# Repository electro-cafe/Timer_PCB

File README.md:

# Timer_PCB
This repository contain all file relative to the PCB of the timer project.

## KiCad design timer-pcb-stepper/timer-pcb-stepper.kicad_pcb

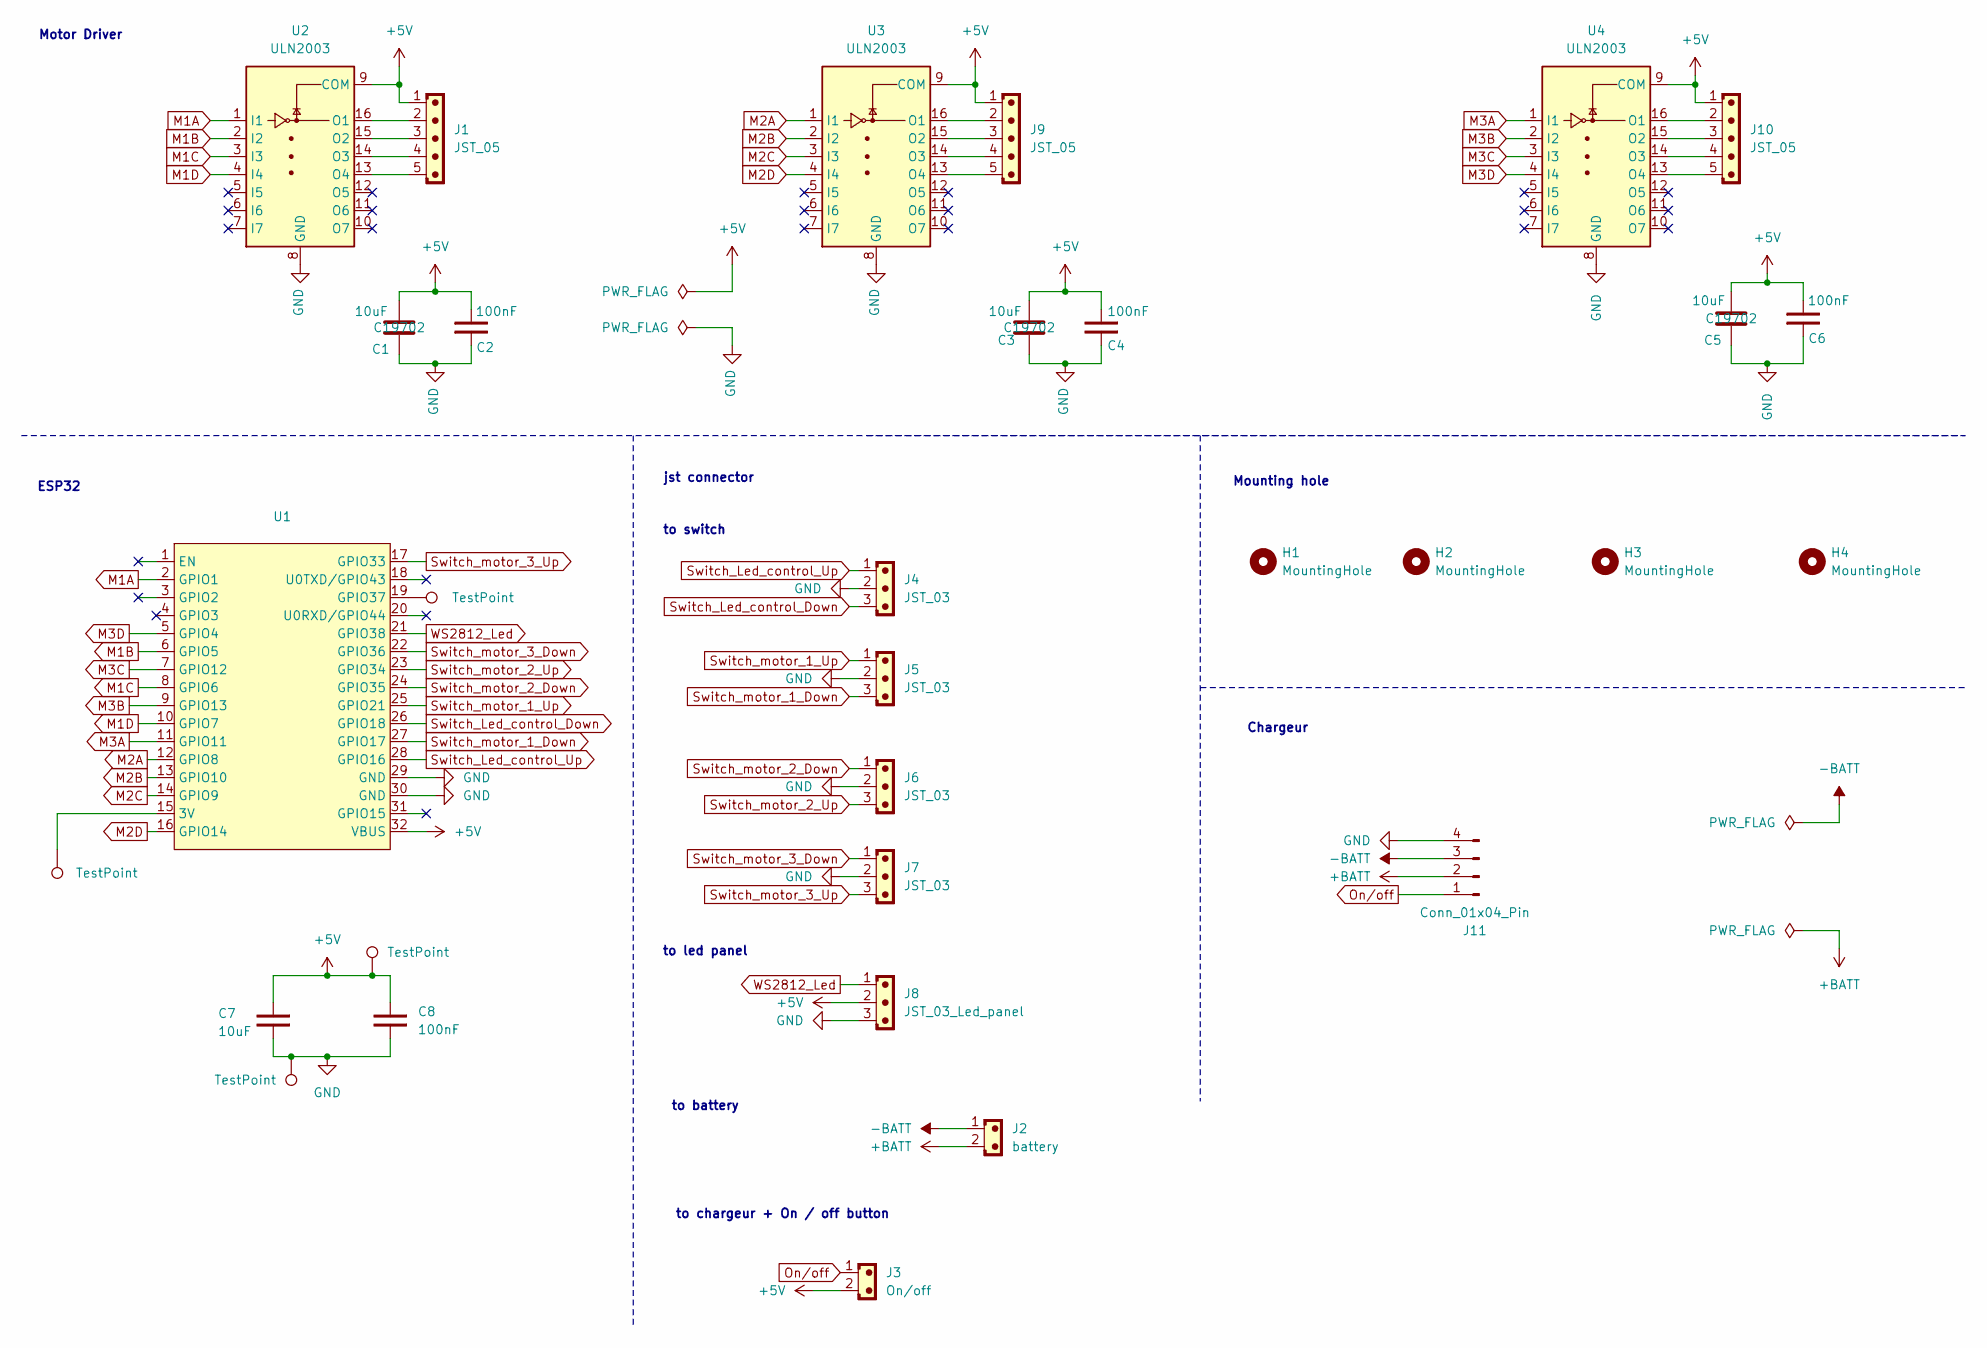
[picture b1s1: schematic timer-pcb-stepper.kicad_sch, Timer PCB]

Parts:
C1, C3, C5, C7: 10uF; C_0805_2012Metric; JLCPCB Part # C19702
C2, C4, C6, C8: 100nF; C_0603_1608Metric; JLCPCB Part # C1525
H1, H2, H3, H4: MountingHole; MountingHole_3.2mm_M3_DIN965_Pad_TopOnly
J1, J9, J10: JST_05; JST_EH_B5B-EH-A_1x05_P2.50mm_Vertical; JLCPCB Part # C157991
J2: battery; JST_XH_B2B-XH-AM_1x02_P2.50mm_Vertical
J3: On/off; JST_XH_B2B-XH-AM_1x02_P2.50mm_Vertical
J4, J5, J6, J7: JST_03; JST_XH_S3B-XH-A-1_1x03_P2.50mm_Horizontal
J8: JST_03_Led_panel; JST_XH_S3B-XH-A-1_1x03_P2.50mm_Horizontal
J11: Conn_01x04_Pin; JST_XA_B04B-XASK-1-A_1x04_P2.50mm_Vertical
TP1, TP2, TP3, TP4: TestPoint; TestPoint_Loop_D2.54mm_Drill1.5mm_Beaded
U1: S3 Mini
U2, U3, U4: ULN2003; SOIC-16_4.55x10.3mm_P1.27mm; LCSC C7512

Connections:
+5V: C1.2, C2.2, C3.2, C4.1, C5.2, C6.2, C7.1, C8.1, J1.1, J3.2, J8.2, J9.1, J10.1, TP2.1, U1.32 (VBUS), U2.9 (COM), U3.9 (COM), U4.9 (COM)
+BATT: J2.2, J11.2
-BATT: J2.1, J11.3
GND: C1.1, C2.1, C3.1, C4.2, C5.1, C6.1, C7.2, C8.2, J4.2, J5.2, J6.2, J7.2, J8.3, J11.4, TP4.1, U1.29 (GND), U1.30 (GND), U2.8 (GND), U3.8 (GND), U4.8 (GND)
M1A: U1.2 (GPIO1), U2.1 (I1)
M1B: U1.6 (GPIO5), U2.2 (I2)
M1C: U1.8 (GPIO6), U2.3 (I3)
M1D: U1.10 (GPIO7), U2.4 (I4)
M2A: U1.12 (GPIO8), U3.1 (I1)
M2B: U1.13 (GPIO10), U3.2 (I2)
M2C: U1.14 (GPIO9), U3.3 (I3)
M2D: U1.16 (GPIO14), U3.4 (I4)
M3A: U1.11 (GPIO11), U4.1 (I1)
M3B: U1.9 (GPIO13), U4.2 (I2)
M3C: U1.7 (GPIO12), U4.3 (I3)
M3D: U1.5 (GPIO4), U4.4 (I4)
unnamed: TP1.1, U1.15 (3V)
unnamed: TP3.1, U1.19 (GPIO37)
unnamed: J1.2, U2.16 (O1)
unnamed: J1.3, U2.15 (O2)
unnamed: J1.4, U2.14 (O3)
unnamed: J1.5, U2.13 (O4)
unnamed: J9.2, U3.16 (O1)
unnamed: J9.3, U3.15 (O2)
unnamed: J9.4, U3.14 (O3)
unnamed: J9.5, U3.13 (O4)
unnamed: J10.2, U4.16 (O1)
unnamed: J10.3, U4.15 (O2)
unnamed: J10.4, U4.14 (O3)
unnamed: J10.5, U4.13 (O4)
On/off: J3.1, J11.1
Switch_Led_control_Down: J4.3, U1.26 (GPIO18)
Switch_Led_control_Up: J4.1, U1.28 (GPIO16)
Switch_motor_1_Down: J5.3, U1.27 (GPIO17)
Switch_motor_1_Up: J5.1, U1.25 (GPIO21)
Switch_motor_2_Down: J6.1, U1.24 (GPIO35)
Switch_motor_2_Up: J6.3, U1.23 (GPIO34)
Switch_motor_3_Down: J7.1, U1.22 (GPIO36)
Switch_motor_3_Up: J7.3, U1.17 (GPIO33)
WS2812_Led: J8.1, U1.21 (GPIO38)

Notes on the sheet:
Mounting hole
to led panel
Motor Driver
to chargeur + On / off button
jst connector
Chargeur
to battery
to switch
ESP32

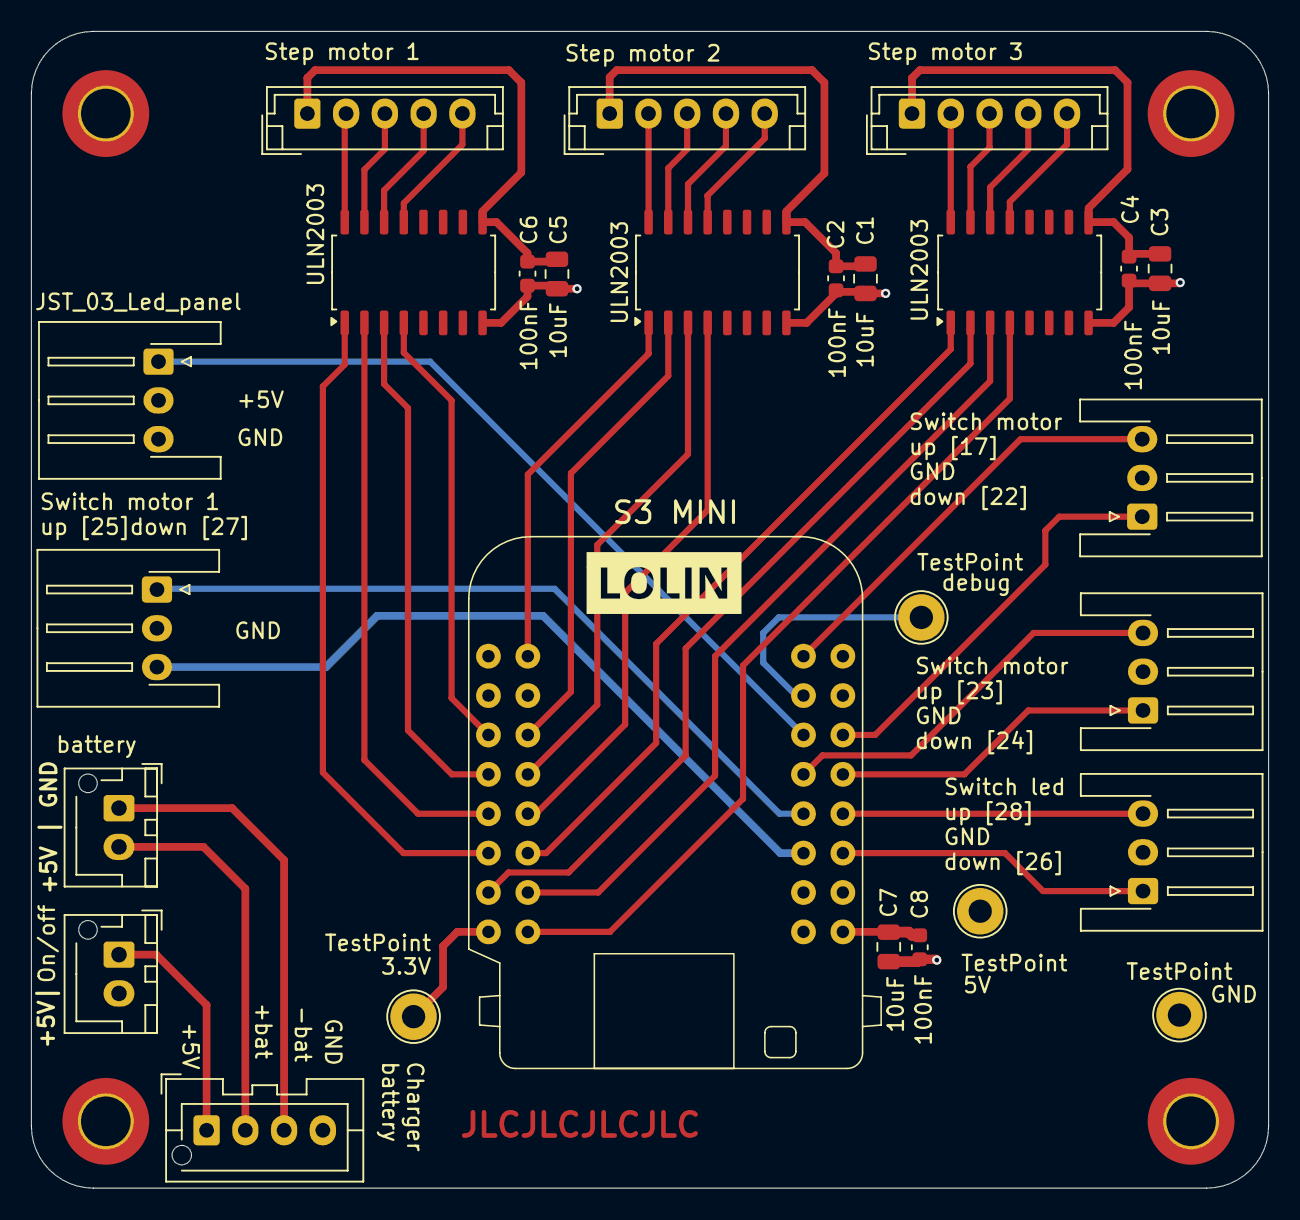
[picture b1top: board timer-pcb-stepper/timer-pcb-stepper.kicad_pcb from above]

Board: 4 copper layers, 79.8 x 74.6 mm, 31 parts (0 on the bottom side), 40 nets.

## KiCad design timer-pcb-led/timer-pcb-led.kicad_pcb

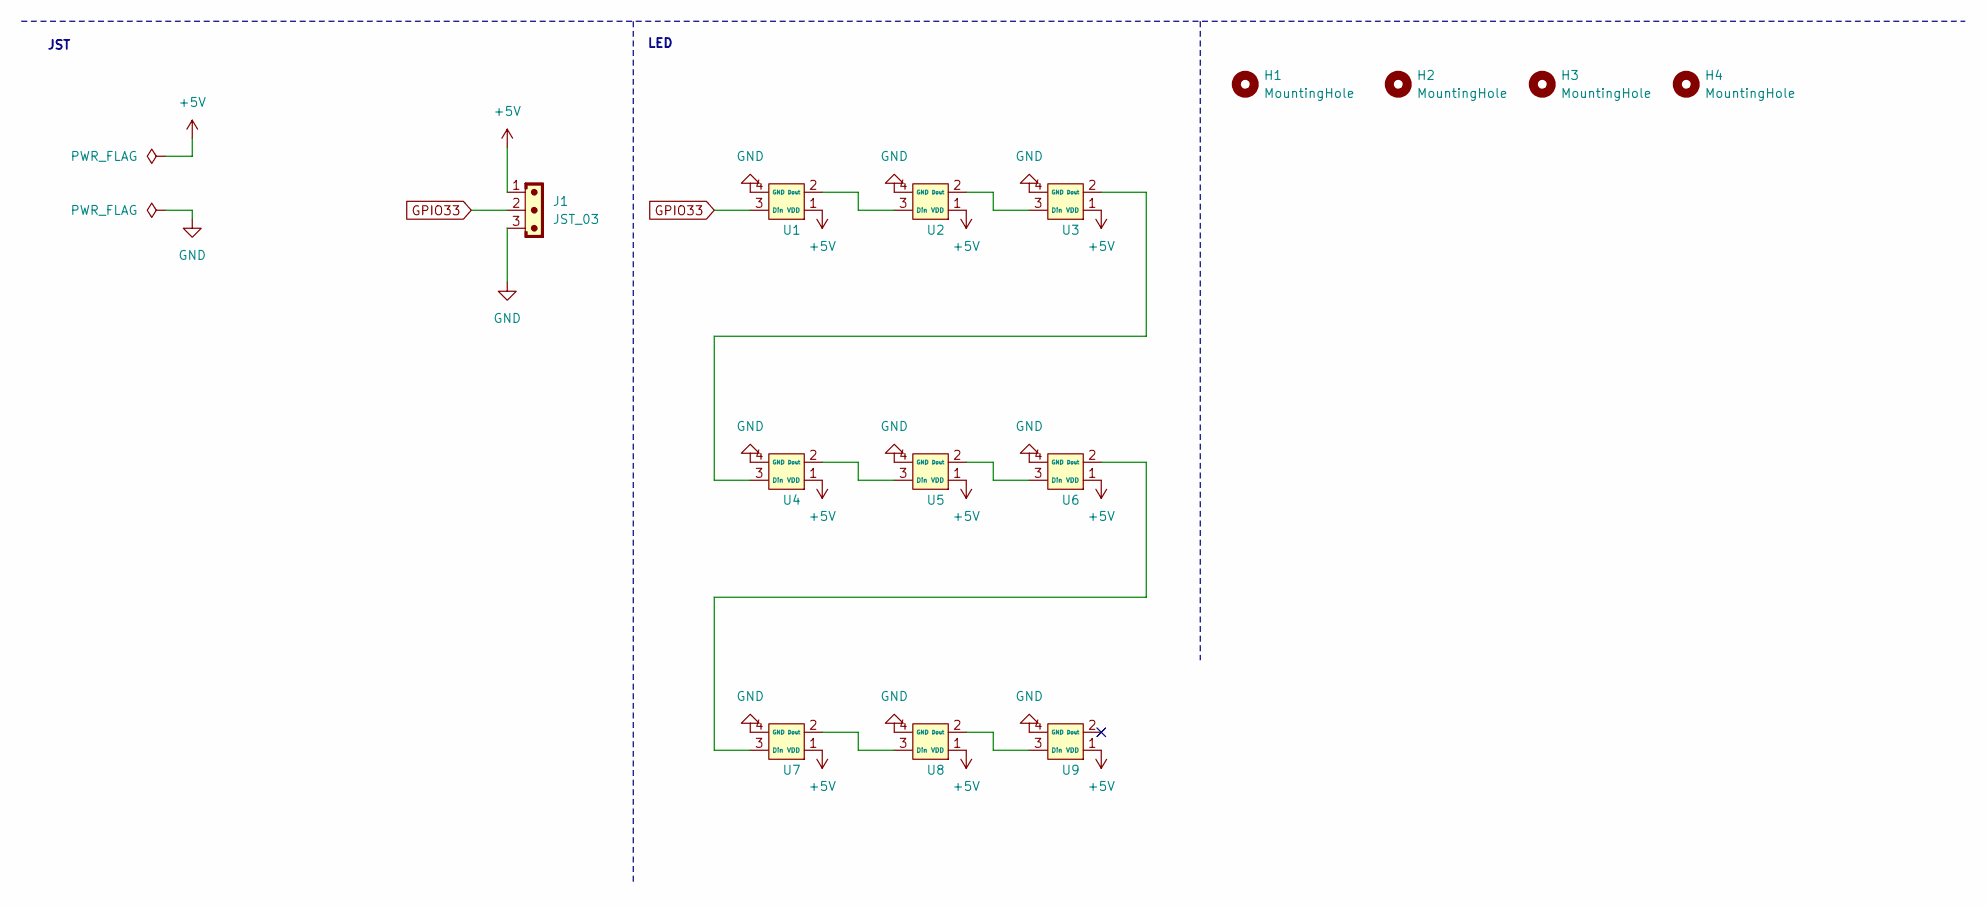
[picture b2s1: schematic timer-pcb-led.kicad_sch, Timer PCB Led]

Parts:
H1, H2, H3, H4: MountingHole; MountingHole_3.2mm_M3_DIN965_Pad_TopOnly
J1: JST_03; JST_XH_S3B-XH-A-1_1x03_P2.50mm_Horizontal
U1, U2, U3, U4, U5, U6, U7, U8, U9: WS2812B-Xinlight-5050RGBC

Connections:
+5V: J1.1, U1.1 (VDD), U2.1 (VDD), U3.1 (VDD), U4.1 (VDD), U5.1 (VDD), U6.1 (VDD), U7.1 (VDD), U8.1 (VDD), U9.1 (VDD)
GND: J1.3, U1.4 (GND), U2.4 (GND), U3.4 (GND), U4.4 (GND), U5.4 (GND), U6.4 (GND), U7.4 (GND), U8.4 (GND), U9.4 (GND)
GPIO33: J1.2, U1.3 (Din)
unnamed: U1.2 (Dout), U2.3 (Din)
unnamed: U2.2 (Dout), U3.3 (Din)
unnamed: U3.2 (Dout), U4.3 (Din)
unnamed: U4.2 (Dout), U5.3 (Din)
unnamed: U5.2 (Dout), U6.3 (Din)
unnamed: U6.2 (Dout), U7.3 (Din)
unnamed: U7.2 (Dout), U8.3 (Din)
unnamed: U8.2 (Dout), U9.3 (Din)

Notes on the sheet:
LED
JST

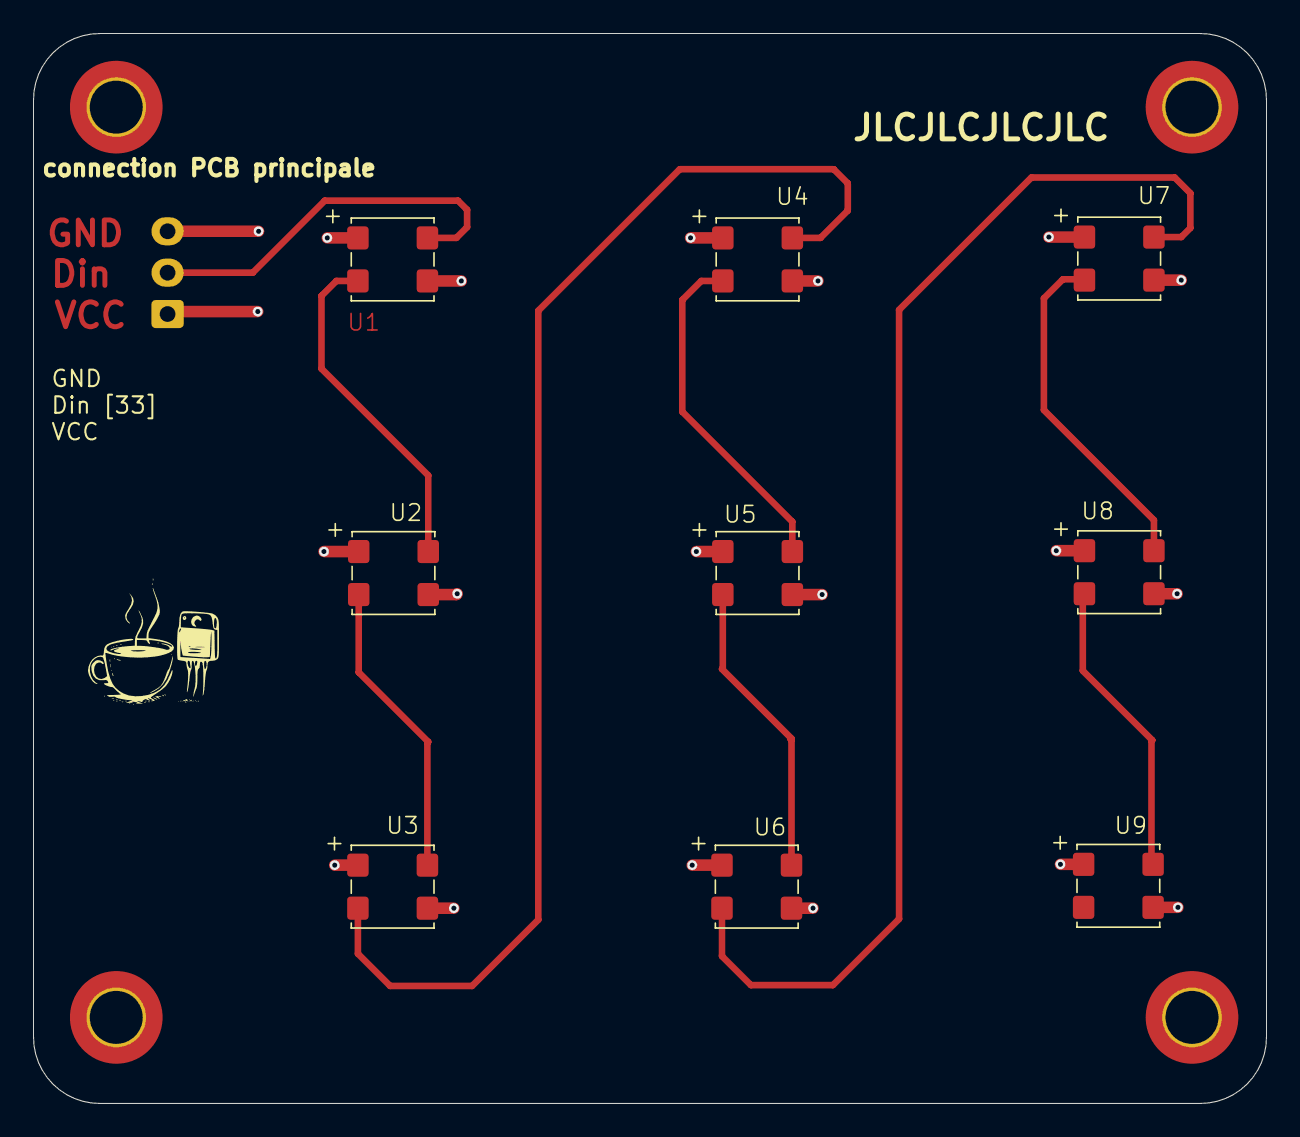
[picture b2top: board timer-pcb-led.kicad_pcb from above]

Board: 4 copper layers, 74.5 x 64.6 mm, 14 parts (1 on the bottom side), 11 nets.

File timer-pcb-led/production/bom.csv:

Designator,Footprint,Quantity,Value,LCSC Part #
U1,WS2812B-Xinlight-5050RGBC,1,,C2843785
"U2, U3, U4, U5, U6, U7, U8, U9",WS2812B-Xinlight-5050RGBC,8,~,C2843785

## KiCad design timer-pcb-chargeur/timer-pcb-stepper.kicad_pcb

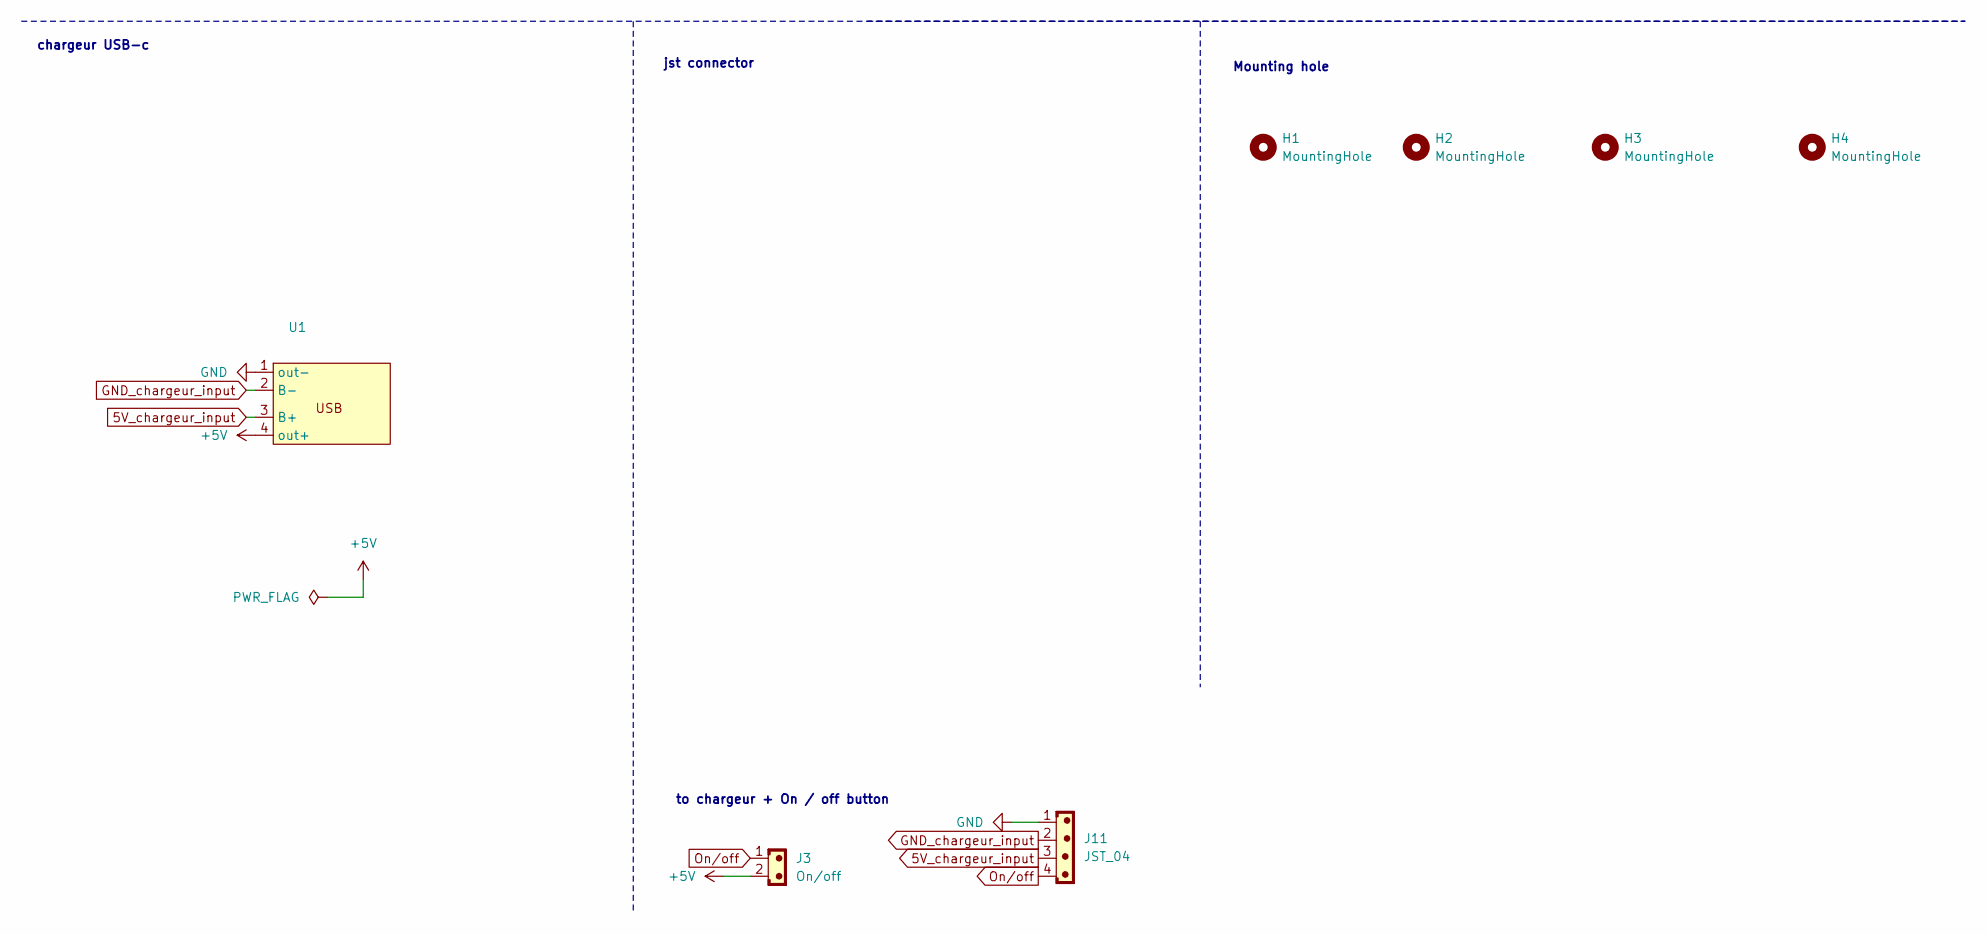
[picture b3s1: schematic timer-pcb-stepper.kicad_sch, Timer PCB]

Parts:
H1, H2, H3, H4: MountingHole; MountingHole_3.2mm_M3_DIN965_Pad_TopOnly
J3: On/off; JST_PH_B2B-PH-K_1x02_P2.00mm_Vertical
J11: JST_04; JST_PH_B4B-PH-K_1x04_P2.00mm_Vertical
U1: TP4056_chargeur_USB-C

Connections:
5V_chargeur_input: J11.3, U1.3 (B+)
+5V: J3.2, U1.4 (out+)
GND: J11.1, U1.1 (out-)
GND_chargeur_input: J11.2, U1.2 (B-)
On/off: J3.1, J11.4

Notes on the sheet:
Mounting hole
to chargeur + On / off button
jst connector
chargeur USB-c

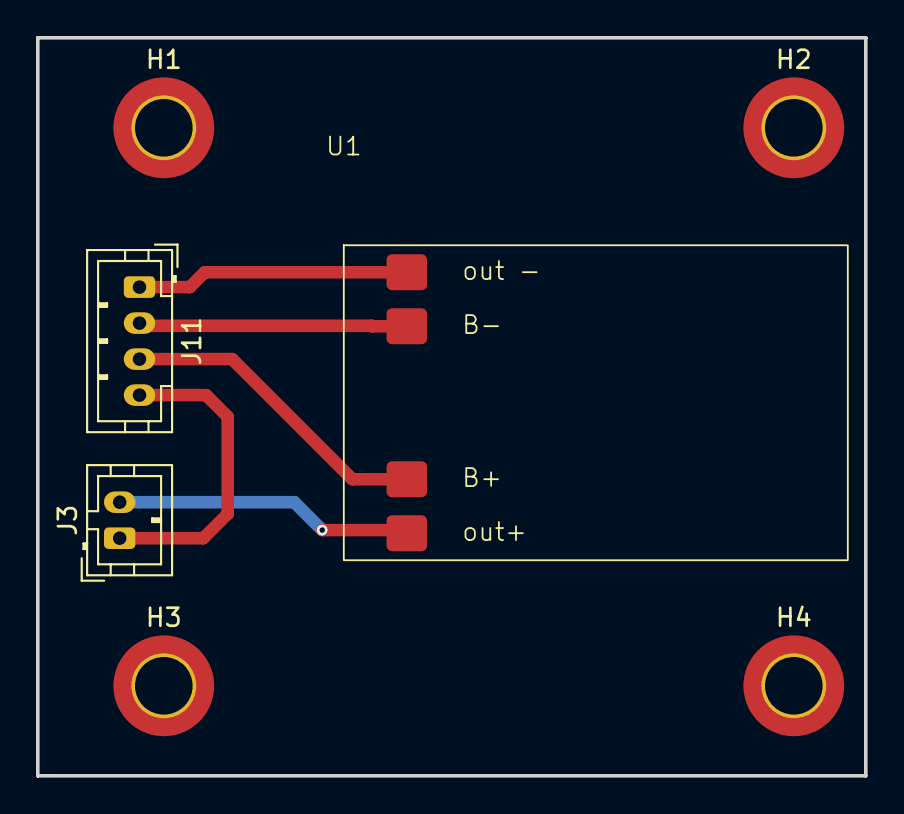
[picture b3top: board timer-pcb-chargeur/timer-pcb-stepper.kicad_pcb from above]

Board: 4 copper layers, 46.0 x 41.0 mm, 7 parts (0 on the bottom side), 5 nets.

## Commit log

2025-05-31 Add KiCad action with Dockerfile, entrypoint script, and workflow configuration
2025-05-31 ajout fichier PCB timer
2025-05-31 Refactor code structure for improved readability and maintainability
2025-06-09 mise à jour des fichiers kicad PCB-led et PCB-stepper. circuit imprimé plus propre et ajout de connecteur jst
2025-06-13 mise à jour des fichiers kicad PCB-stepper. circuit imprimé plus propre et ajout de connecteur jst
2025-06-16 rework des PCB stepper et led. création du PCB chargeur
2025-06-16 mise à jour fichier kicad stepper + led. création dossier chargeur PCB.création du fichier .rpt
2025-06-18 Fix report file names in ERC and DRC functions to include correct suffixes
2025-06-18 Remove branch restriction for push events in PCB workflow
2025-06-19 test comit avec que dossier led
2025-06-20 ajout des dossier chargeur et led au projet
2025-06-20 suppression du dossier chargeur. integration de la partie chargeur usb-c sur le PCB stepper
2025-06-26 reroutage des liaisons pour avoir un circuit imprimé plus propre.
2025-06-30 ajout de text indicatif couche silkscreen sur les différents composants du PCB. ajout de test points sur 5V, GND, GPIO37 pour debugger et pin 15 (3.3V). connecteurs repositionés franc bord.
2025-07-01 ajout de text indicatif des composants, ajout de signe + et - sur la connection batterie, déplacement des connecteurs franc bord, ajout de testpoint, modification du déplacement du condensateur de dé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
2025-08-12 mise à jour fichier blender pour impression 3D. Reste a mettre la bonne épaisseur pour le socle de la shell et percer les trous pour interrupteurs switch et on-off. déterminer ou placer entrées pour 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
